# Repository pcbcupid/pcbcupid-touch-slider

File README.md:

# pcbcupid-touch-slider
Touch slider capable of handling 3 touch input with adjustable sensitivity!

This repo contains open source PCB files for PCBCUPID GSense Touch Slider Module <br/>
This particular PCB is designed using Kicad v9.0

**This design has been built and tested successfully!**
For more details, check out the product pages at

   * [Gsesnse-ICS43434](https://shop.pcbcupid.com/product/gs001/)
   * [Docs](https://learn.pcbcupid.com/boards/g-sense/ics43434)
     
We are here to build India's largest open source hardware community, If you like to support
please consider buying the product from the above link!

[Creative Commons Attribution, Share-Alike license](https://creativecommons.org/licenses/by-sa/4.0/deed.en)
All text above must be included in any redistribution

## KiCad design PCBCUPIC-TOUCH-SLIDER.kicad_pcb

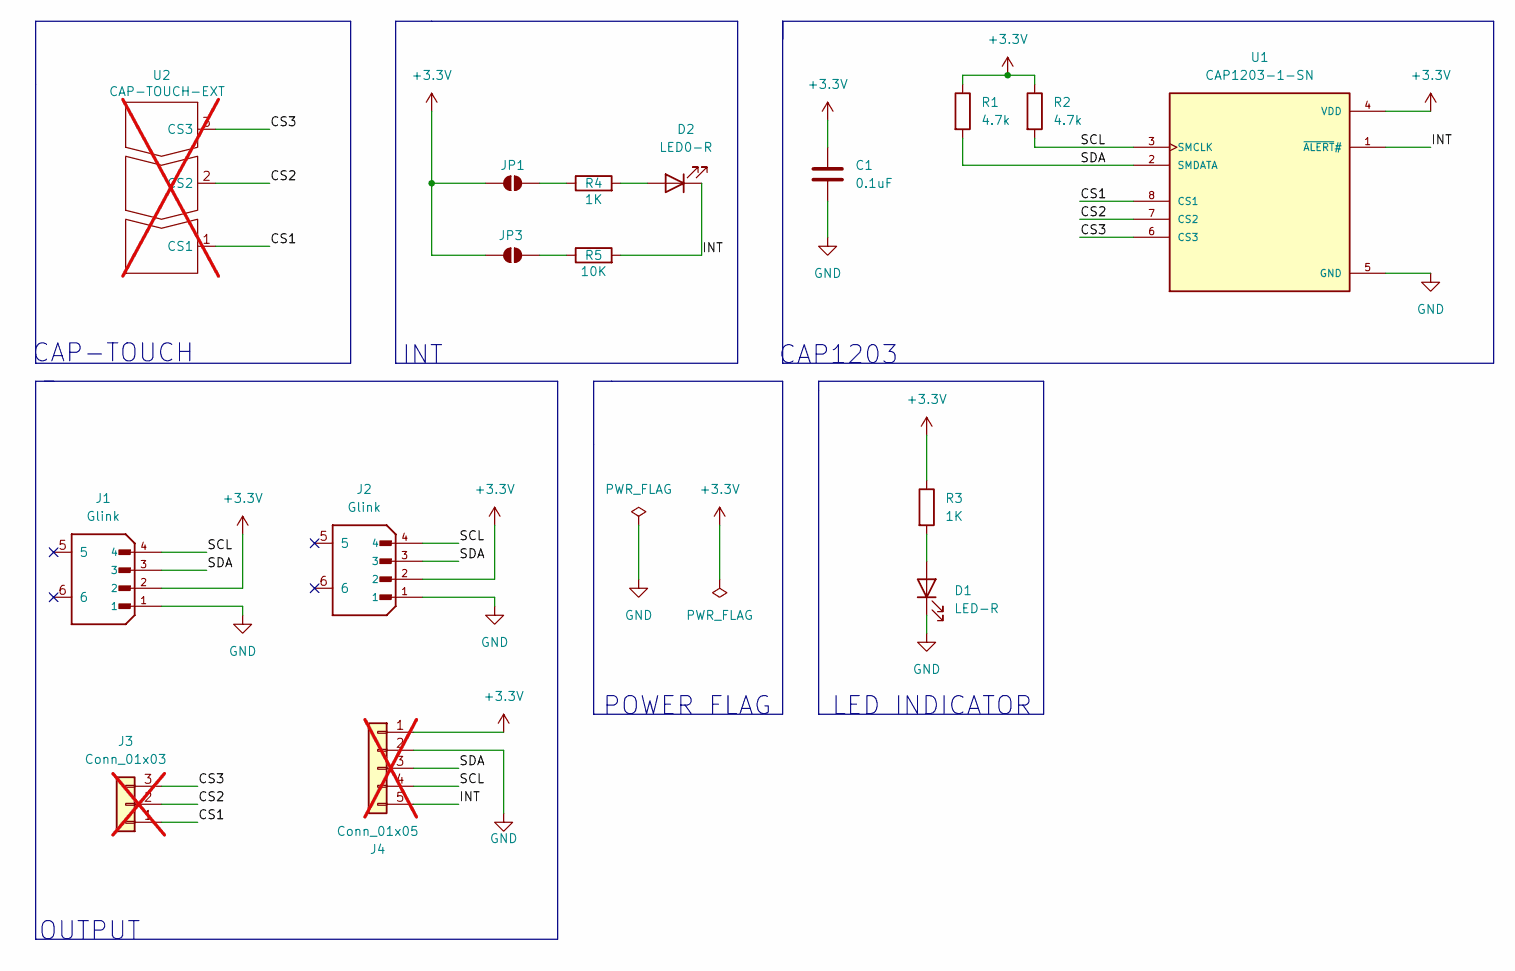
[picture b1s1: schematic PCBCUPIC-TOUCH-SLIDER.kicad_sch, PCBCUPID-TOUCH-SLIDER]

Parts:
C1: 0.1uF; C_0603_1608Metric
D1: LED-R; LED_0603_1608Metric
D2: LED0-R; LED_0603_1608Metric
J1, J2: Glink; SPARKFUN_PRT-14417; PARTREV NA
J3: Conn_01x03; PinHeader_1x03_P2.54mm_Vertical; not fitted
J4: Conn_01x05; PinHeader_1x05_P2.54mm_Vertical; not fitted
JP1, JP3: SolderJumper_2_Open; SolderJumper-2_P1.3mm_Open_RoundedPad1.0x1.5mm
R1, R2: 4.7k; R_0603_1608Metric
R3, R4: 1K; R_0603_1608Metric
R5: 10K; R_0603_1608Metric
U1: CAP1203-1-SN; SOIC127P600X175-8N; PARTREV A
U2: CAP-TOUCH-EXT; TouchSlider-3_40x12mm; not fitted

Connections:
+3.3V: C1.1, J1.2, J2.2, J4.1, JP1.2 (B), JP3.2 (B), R1.1, R2.1, R3.1, U1.4 (VDD)
/CS1: J3.1, U1.8 (CS1), U2.1 (CS1)
/CS2: J3.2, U1.7 (CS2), U2.2 (CS2)
/CS3: J3.3, U1.6 (CS3), U2.3 (CS3)
/INT: D2.1 (K), J4.5, R5.2, U1.1 (~ALERT#)
/SCL: J1.4, J2.4, J4.4, R2.2, U1.3 (SMCLK)
/SDA: J1.3, J2.3, J4.3, R1.2, U1.2 (SMDATA)
GND: C1.2, D1.1 (K), J1.1, J2.1, J4.2, U1.5 (GND)
unnamed: D1.2 (A), R3.2
unnamed: D2.2 (A), R4.2
unnamed: JP1.1 (A), R4.1
unnamed: JP3.1 (A), R5.1

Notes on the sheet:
CAP-TOUCH
POWER FLAG
LED INDICATOR
CAP1203
INT
OUTPUT

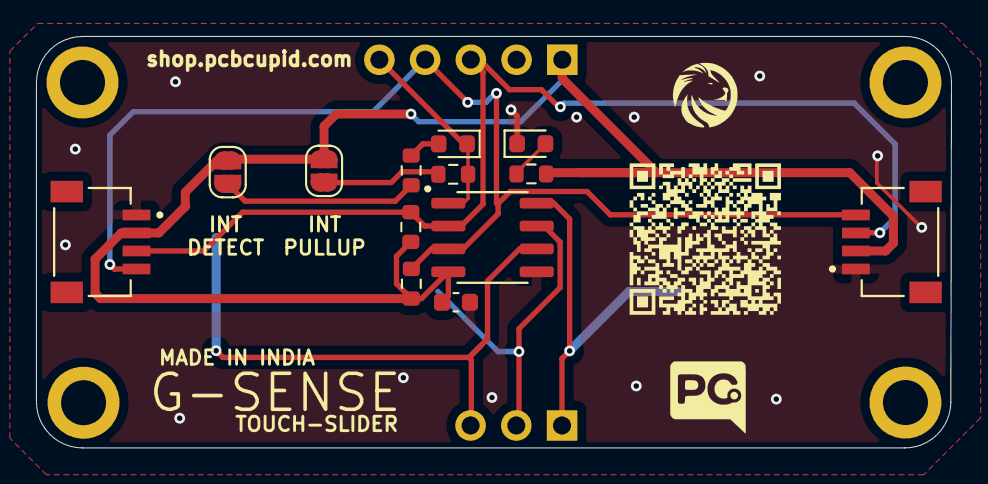
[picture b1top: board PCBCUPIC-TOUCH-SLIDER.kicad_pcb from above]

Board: 2 copper layers, 50.8 x 22.9 mm, 16 parts (1 on the bottom side), 12 nets.

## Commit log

2025-09-27 Revert "Update README.md"
    This reverts commit de8c0cea9ae4e6f83bcd65494965e3f9e67ab9aa.
